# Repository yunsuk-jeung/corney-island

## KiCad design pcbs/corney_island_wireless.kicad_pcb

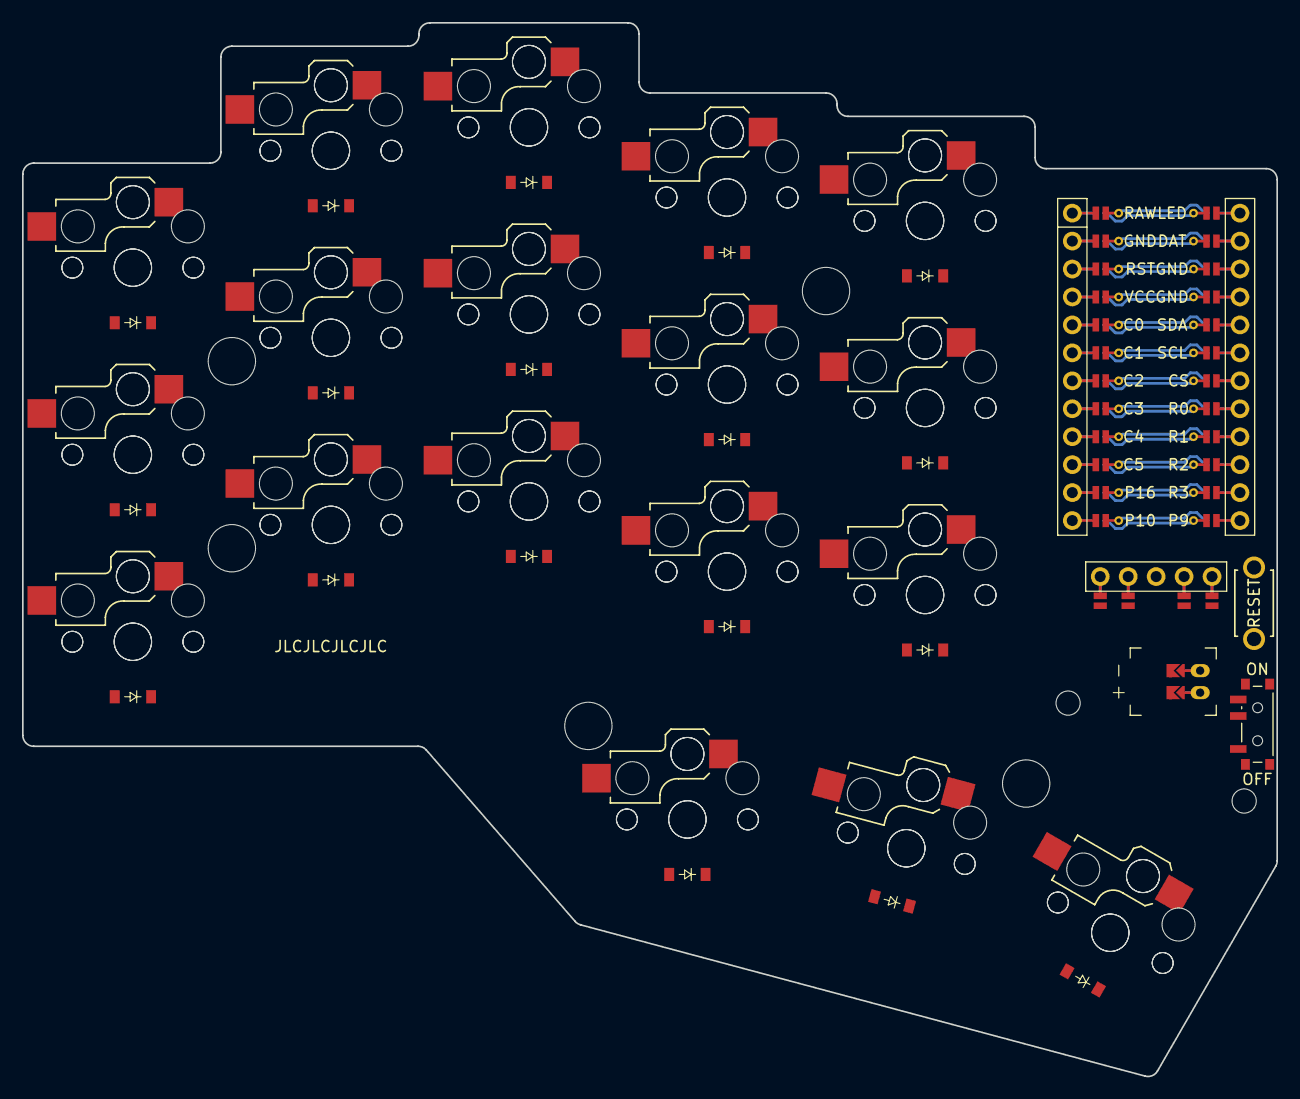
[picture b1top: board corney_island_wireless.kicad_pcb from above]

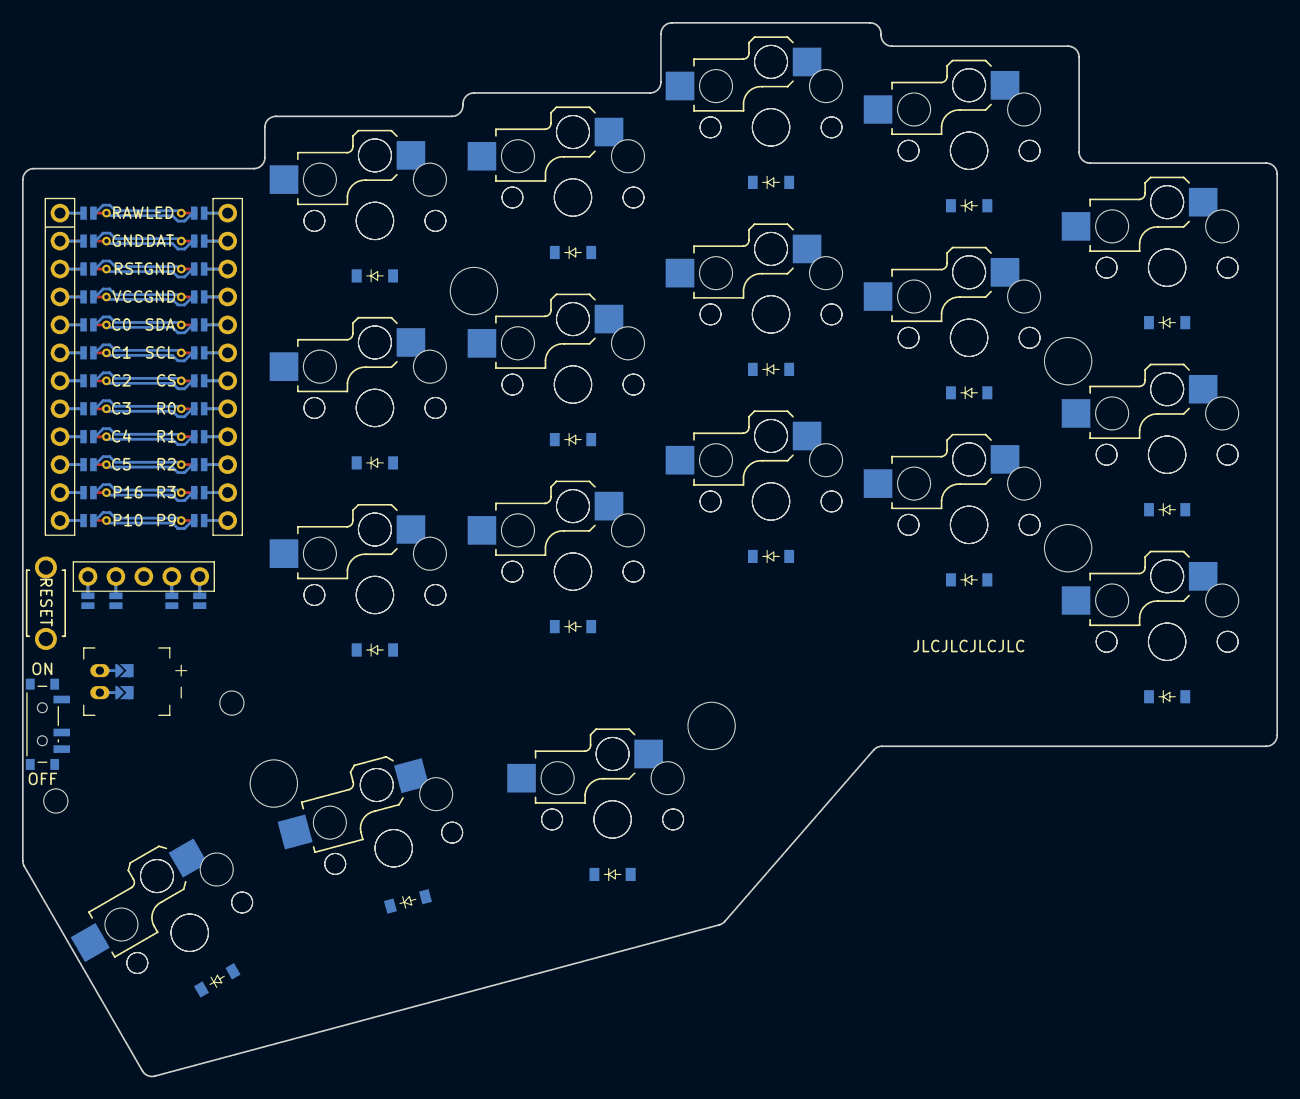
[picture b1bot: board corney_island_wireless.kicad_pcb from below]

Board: 2 copper layers, 114.0 x 95.8 mm, 84 parts (36 on the bottom side), 71 nets.

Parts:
B1: ResetSW
D1, D2, D3, D4, D5, D6, D7, D8, D9, D10, D11, D12, D13, D14, D15, D16, D17, D18, D19, D20, D21, D22, D23, D24, D25, D26, D27, D28, D29, D30, D31, D32, D33, D34, D35, D36: diode_tht_sod123
DISP1: display_nice_view
JST1: battery_connector_jst_ph_2
MCU1: mcu_nice_nano
MH1, MH2, MH3, MH4, MH5, MH6, MH7: mounting_hole_npth
PWR1: power_switch_smd_side
S1, S2, S3, S4, S5, S6, S7, S8, S9, S10, S11, S12, S13, S14, S15, S16, S17, S18, S19, S20, S21, S22, S23, S24, S25, S26, S27, S28, S29, S30, S31, S32, S33, S34, S35, S36: switch_choc_v1_v2

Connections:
BAT_P: JST1.1, PWR1.1, PWR1.3
C1: MCU1.119, S1.1, S2.1, S3.1, S19.1, S20.1, S21.1
C2: MCU1.118, S4.1, S5.1, S6.1, S22.1, S23.1, S24.1
C3: MCU1.117, S7.1, S8.1, S9.1, S16.1, S25.1, S26.1, S27.1, S34.1
C4: MCU1.116, S10.1, S11.1, S12.1, S17.1, S28.1, S29.1, S30.1, S35.1
C5: MCU1.115, S13.1, S14.1, S15.1, S18.1, S31.1, S32.1, S33.1, S36.1
CS: DISP1.10, DISP1.20, MCU1.107
DISP1_1: DISP1.1, DISP1.14, DISP1.27
DISP1_2: DISP1.2, DISP1.15, DISP1.26
DISP1_4: DISP1.4, DISP1.16, DISP1.25
DISP1_5: DISP1.5, DISP1.17, DISP1.24
GND: B1.2, DISP1.11, DISP1.21, JST1.2, MCU1.103, MCU1.104, MCU1.123
JST1_1: JST1.11, JST1.21, JST1.31
JST1_2: JST1.12, JST1.22, JST1.32
MCU1_1: MCU1.1, MCU1.24
MCU1_2: MCU1.2, MCU1.23
MCU1_3: MCU1.3, MCU1.22
MCU1_4: MCU1.4, MCU1.21
MCU1_5: MCU1.5, MCU1.20
MCU1_6: MCU1.6, MCU1.19
MCU1_7: MCU1.7, MCU1.18
MCU1_8: MCU1.8, MCU1.17
MCU1_9: MCU1.9, MCU1.16
MCU1_10: MCU1.10, MCU1.15
MCU1_11: MCU1.11, MCU1.14
MCU1_12: MCU1.12, MCU1.13
MOSI: DISP1.13, DISP1.23
R0: D3.1, D6.1, D9.1, D12.1, D15.1, D21.1, D24.1, D27.1, D30.1, D33.1, MCU1.108
R1: D2.1, D5.1, D8.1, D11.1, D14.1, D20.1, D23.1, D26.1, D29.1, D32.1, MCU1.109
R2: D1.1, D4.1, D7.1, D10.1, D13.1, D19.1, D22.1, D25.1, D28.1, D31.1, MCU1.110
R3: D16.1, D17.1, D18.1, D34.1, D35.1, D36.1, MCU1.111
RAW: MCU1.124, PWR1.2
RST: B1.1, MCU1.122
SCK: DISP1.12, DISP1.22
VCC: DISP1.3, MCU1.121
far_home_B: D18.2, S18.2
far_home_F: D36.2, S36.2
index_bottom_B: D10.2, S10.2
index_bottom_F: D28.2, S28.2
index_home_B: D11.2, S11.2
index_home_F: D29.2, S29.2
index_top_B: D12.2, S12.2
index_top_F: D30.2, S30.2
inner_bottom_B: D13.2, S13.2
inner_bottom_F: D31.2, S31.2
inner_home_B: D14.2, S14.2
inner_home_F: D32.2, S32.2
inner_top_B: D15.2, S15.2
inner_top_F: D33.2, S33.2
mid_home_B: D17.2, S17.2
mid_home_F: D35.2, S35.2
middle_bottom_B: D7.2, S7.2
middle_bottom_F: D25.2, S25.2
middle_home_B: D8.2, S8.2
middle_home_F: D26.2, S26.2
middle_top_B: D9.2, S9.2
middle_top_F: D27.2, S27.2
near_home_B: D16.2, S16.2
near_home_F: D34.2, S34.2
pinky_bottom_B: D1.2, S1.2
pinky_bottom_F: D19.2, S19.2
pinky_home_B: D2.2, S2.2
pinky_home_F: D20.2, S20.2
pinky_top_B: D3.2, S3.2
pinky_top_F: D21.2, S21.2
ring_bottom_B: D4.2, S4.2
ring_bottom_F: D22.2, S22.2
ring_home_B: D5.2, S5.2
ring_home_F: D23.2, S23.2
ring_top_B: D6.2, S6.2
ring_top_F: D24.2, S24.2

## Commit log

2024-11-26 to choc space
2024-11-26 working on 3x5
2024-11-26 working
2024-11-26 working on padding
2024-11-28 autorouting working
2024-11-28 change skrew location
2024-11-28 josukey layout
2024-11-28 fixed layout
2024-11-28 mcu loc change
2024-11-28 add intersection code
2024-11-30 add reset / change nice view to oled
2024-12-25 ordered and working nicely.. need some adjustments
2024-12-29 display chage
2025-01-08 staggero_change
2025-03-01 update case
